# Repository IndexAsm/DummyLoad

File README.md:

# Electronic Load
A high-power, water-cooled electronic load designed for testing power supplies, batteries, converters, and other high-power electronics.

## [Board Preview]([https://kicanvas.org/?repo=https%3A%2F%2Fgithub.com%2FIndexAsm%2FDummyLoad](https://kicanvas.org/?repo=https%3A%2F%2Fgithub.com%2FIndexAsm%2FDummyLoad%2Ftree%2Fmain%2FPCB))
Note: There is a bug in the preview. It displays components from the control board next to power board, even though they are deleted in the project.

## Features
* **2 kW maximum power**
* **60 V maximum input voltage**
* **50 A maximum load current**
* **Water-cooled power stage**
* Constant-current (CC) regulation
* Multiple current ranges for improved resolution
* Designed for continuous high-power operation
* Custom-built control and measurement electronics

## Specifications

| Parameter       |             Specification |
| --------------- | ------------------------: |
| Maximum Power   |                  **2 kW** |
| Maximum Voltage |                  **60 V** |
| Maximum Current |                  **50 A** |
| Cooling         |         **Water cooling** |
| Regulation Mode | **Constant Current (CC)** |

### CC Regulation Ranges

| Current Range | Resolution |
| ------------: | ---------: |
|        0–50 A |     100 mA |
|        0–10 A |      25 mA |
|         0–5 A |      10 mA |

The selectable current ranges provide finer control at lower currents while maintaining the full **50 A** capability when required.

## Functions

* **Constant-current load (CC)**
* Selectable current ranges
* Input voltage measurement
* Load current measurement
* Power measurement
* Water-cooling system
* High-power continuous-load operation

## Applications

This electronic load is intended for testing:

* Linear and switching power supplies
* DC-DC converters
* Battery systems
* USB power supplies
* High-current power sources
* Custom power electronics

## [BOM](BOM.csv)
Total is around 600zł -> 160$

## Gallery

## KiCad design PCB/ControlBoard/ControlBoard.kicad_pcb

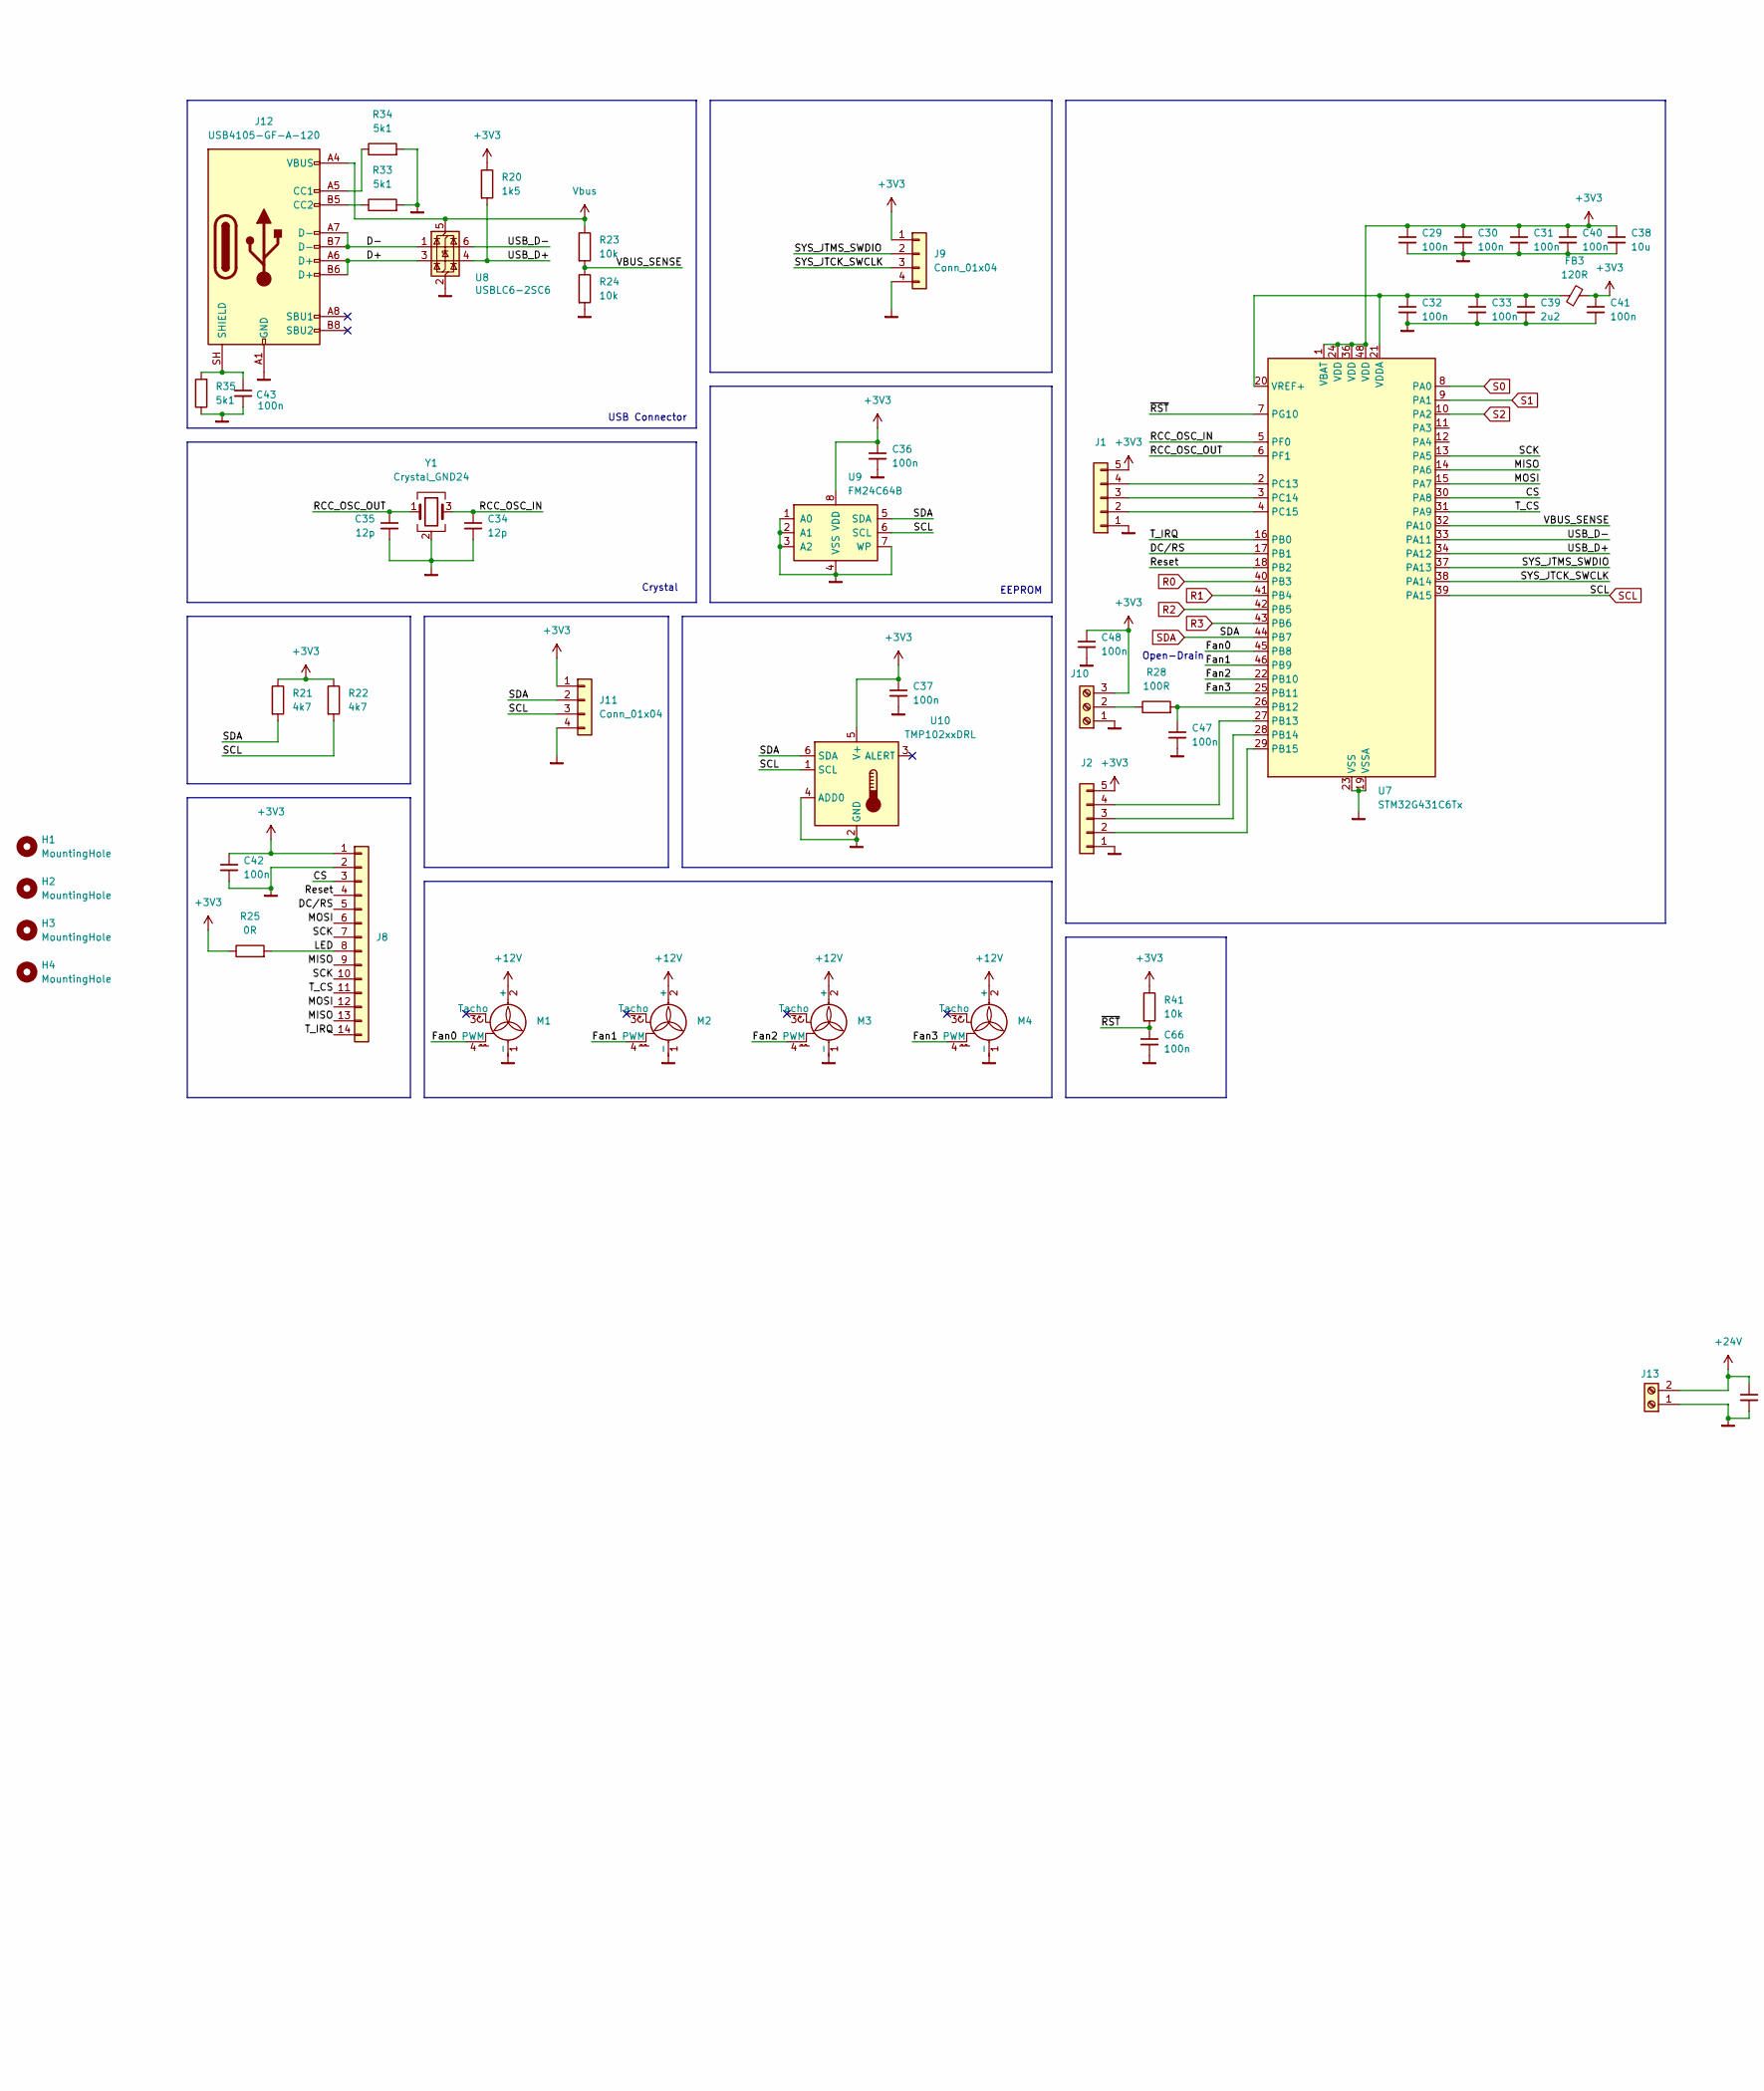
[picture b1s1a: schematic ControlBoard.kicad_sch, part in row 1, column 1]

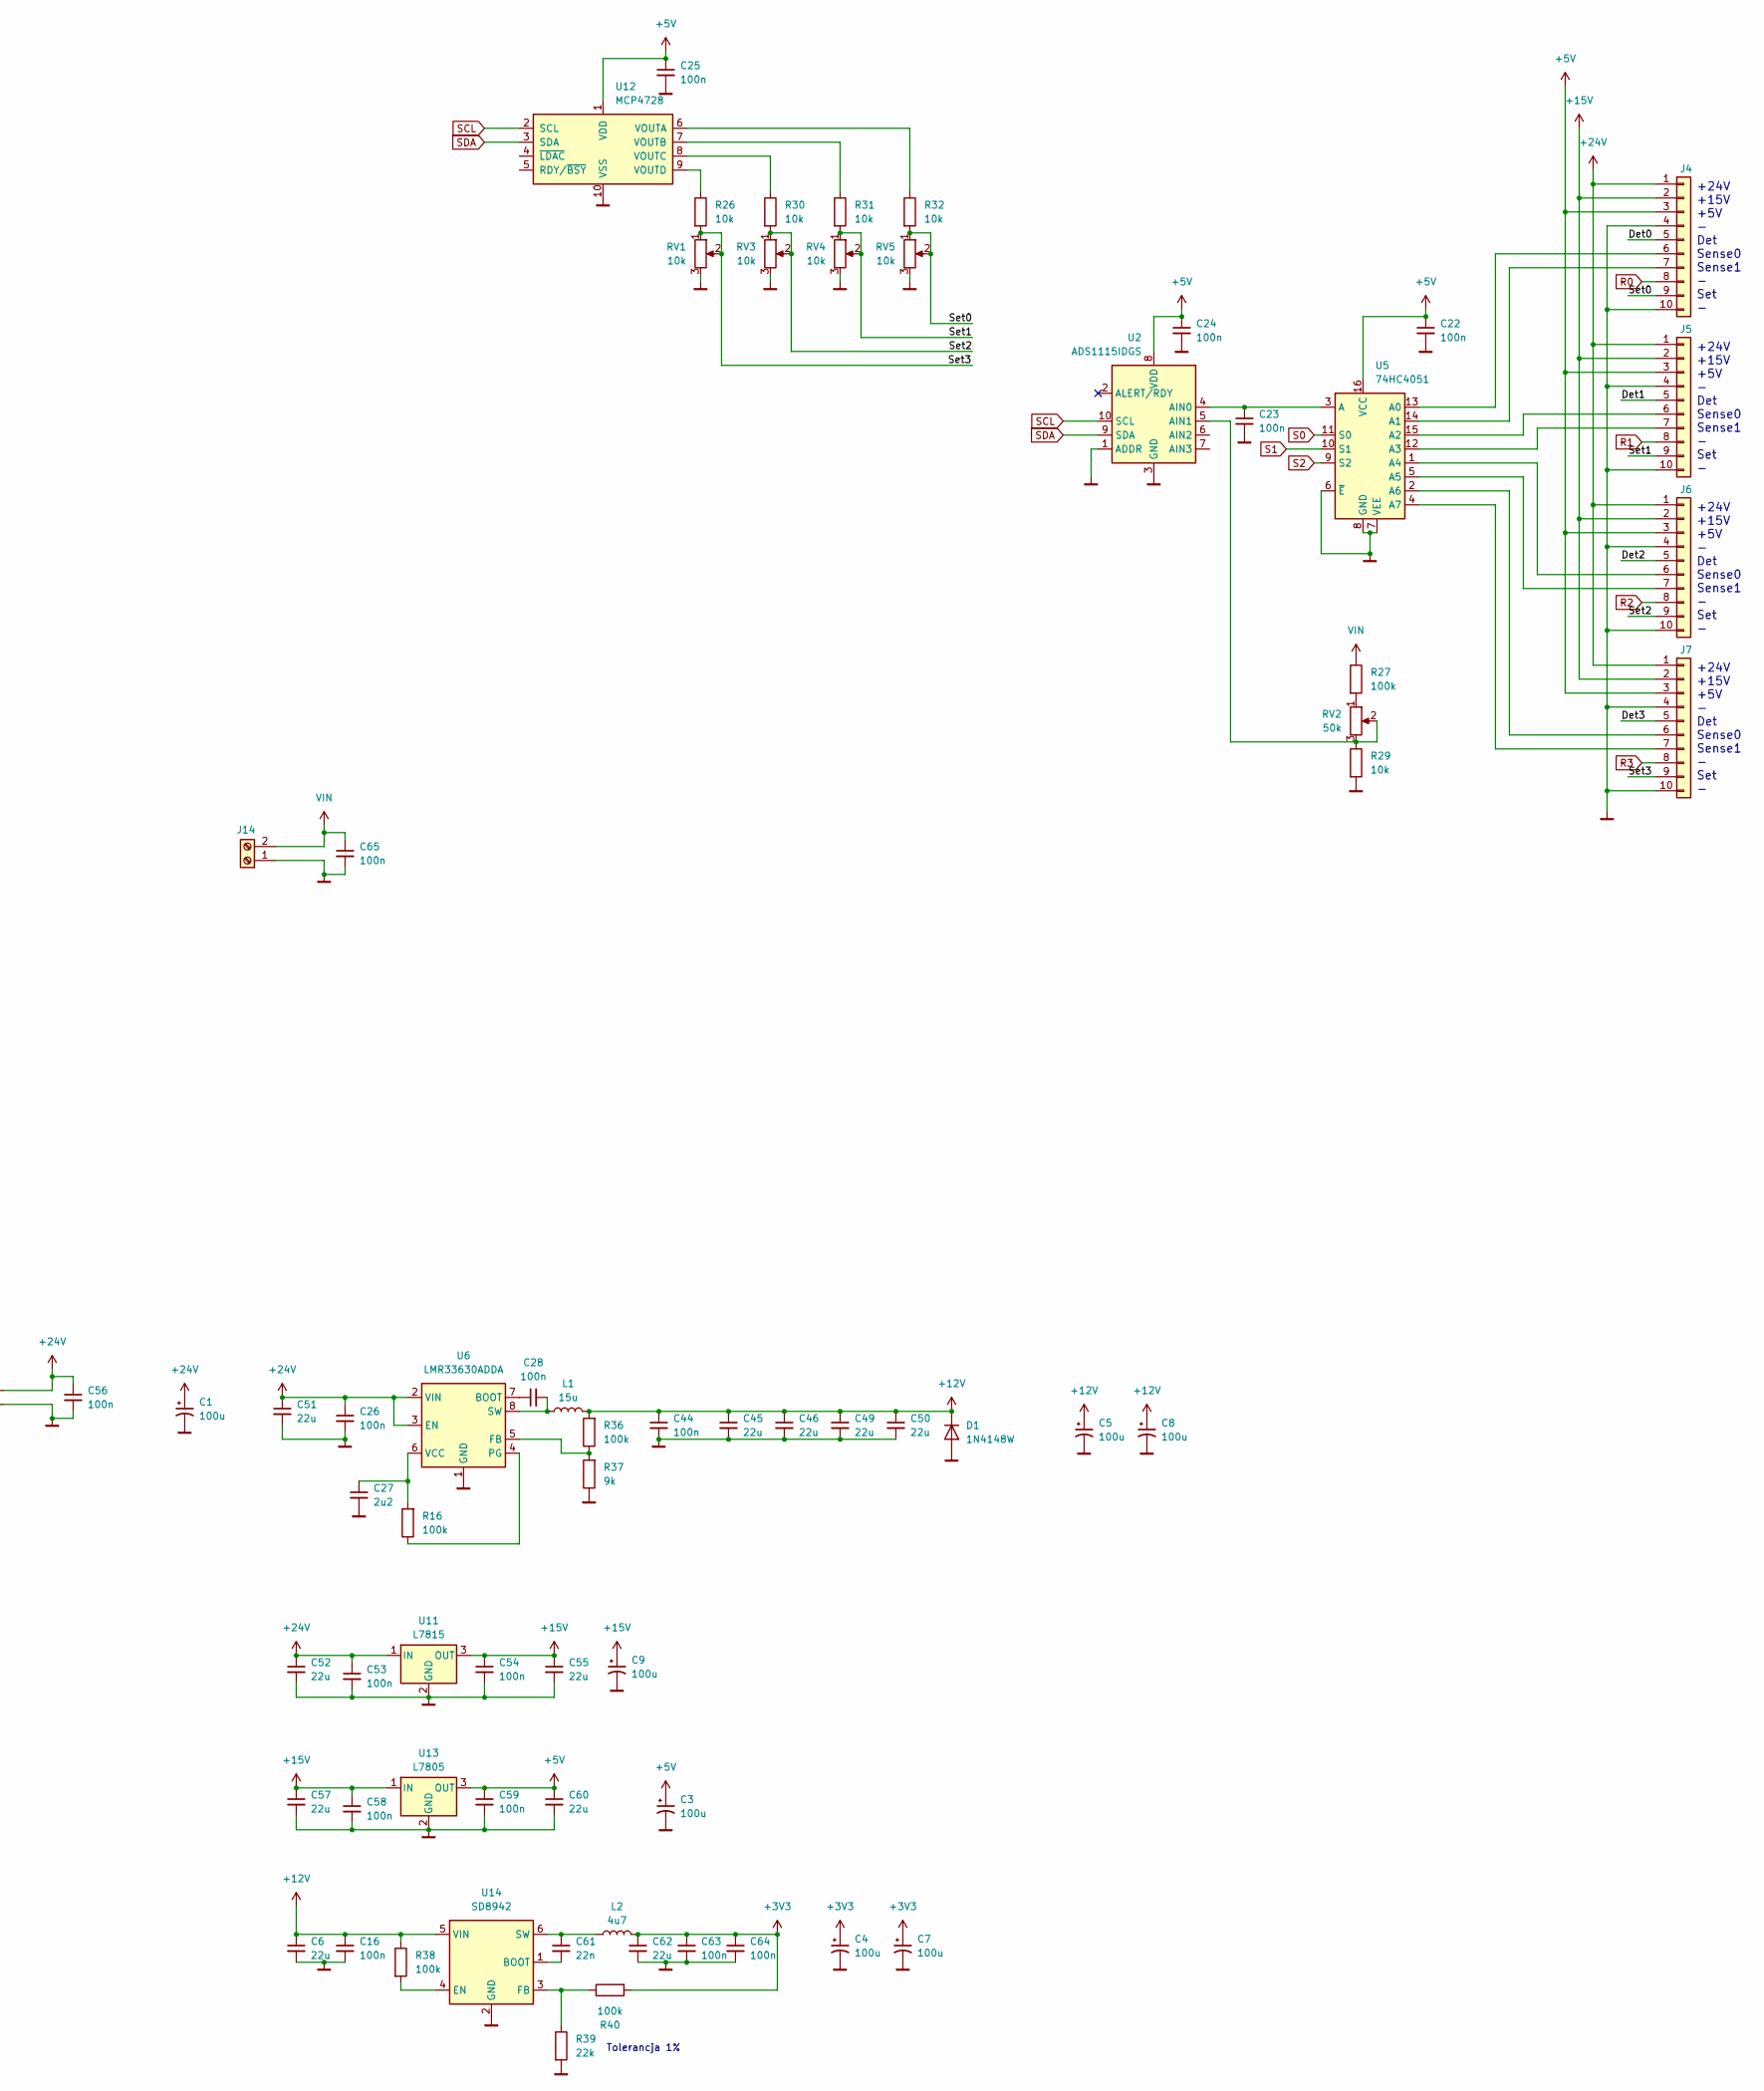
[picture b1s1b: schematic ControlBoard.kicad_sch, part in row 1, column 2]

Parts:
C1, C3, C4, C5, C7, C8, C9: 100u; CP_Radial_D6.3mm_P2.50mm
C6, C45, C46, C49, C50, C51, C52, C55, C57, C60, C62: 22u; C_1206_3216Metric
C16, C22, C23, C24, C25, C26, C28, C29, C30, C31, C32, C33, C36, C37, C40, C41, C42, C43, C44, C47, C48, C53, C54, C56, C58, C59, C63, C64, C65, C66: 100n; C_0603_1608Metric
C27, C39: 2u2; C_0603_1608Metric
C34, C35: 12p; C_0603_1608Metric
C38: 10u; C_0805_2012Metric
C61: 22n; C_0603_1608Metric
D1: 1N4148W; D_SOD-123
FB3: 120R; L_0603_1608Metric
H1, H2, H3, H4: MountingHole; MountingHole_3.2mm_M3
J1, J2: Conn_01x05; PinHeader_1x05_P2.54mm_Vertical
J4, J5, J6, J7: Conn_01x10; PinHeader_1x10_P2.54mm_Vertical
J8: Conn_01x14; PinHeader_1x14_P2.54mm_Vertical
J9, J11: Conn_01x04; PinHeader_1x04_P2.54mm_Vertical
J10: Screw_Terminal_01x03; PinHeader_1x03_P2.54mm_Vertical
J12: USB4105-GF-A-120; USB_C_Receptacle_G-Switch_GT-USB-7010ASV
J13, J14: Screw_Terminal_01x02; TerminalBlock_MaiXu_MX126-5.0-02P_1x02_P5.00mm
L1: 15u; L_APV_APH1240
L2: 4u7; L_APV_ANR5040
M1, M2, M3, M4: Fan_4pin; FanPinHeader_1x04_P2.54mm_Vertical
R16, R27, R36, R38, R40: 100k; R_0603_1608Metric
R20: 1k5; R_0603_1608Metric
R21, R22: 4k7; R_0603_1608Metric
R23, R24, R26, R29, R30, R31, R32, R41: 10k; R_0603_1608Metric
R25: 0R; R_0603_1608Metric
R28: 100R; R_0603_1608Metric
R33, R34, R35: 5k1; R_0603_1608Metric
R37: 9k; R_0603_1608Metric
R39: 22k; R_0603_1608Metric
RV1, RV3, RV4, RV5: 10k; Potentiometer_Bourns_3296W_Vertical
RV2: 50k; Potentiometer_Bourns_3296W_Vertical
U2: ADS1115IDGS; TSSOP-10_3x3mm_P0.5mm
U5: 74HC4051; SOIC-16_3.9x9.9mm_P1.27mm
U6: LMR33630ADDA; Texas_HSOP-8-1EP_3.9x4.9mm_P1.27mm_ThermalVias
U7: STM32G431C6Tx; LQFP-48_7x7mm_P0.5mm
U8: USBLC6-2SC6; SOT-23-6
U9: FM24C64B; SOIC-8_3.9x4.9mm_P1.27mm
U10: TMP102xxDRL; SOT-563
U11: L7815; TO-252-2
U12: MCP4728; MSOP-10_3x3mm_P0.5mm
U13: L7805; TO-252-2
U14: SD8942; SOT-23-6
Y1: Crystal_GND24; Crystal_SMD_EuroQuartz_X22-4Pin_2.5x2.0mm_HandSoldering

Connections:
+3V3: C4.1, C7.1, C29.1, C30.1, C31.1, C36.1, C37.1, C38.1, C40.1, C41.1, C42.1, C48.1, C62.1, C63.1, C64.1, FB3.2, J1.5, J2.5, J8.1, J9.1, J10.3, J11.1, L2.2, R20.1, R21.1, R22.1, R25.1, R40.2, R41.1, U7.1 (VBAT), U7.24 (VDD), U7.36 (VDD), U7.48 (VDD), U9.8 (VDD), U10.5 (V+)
+5V: C3.1, C22.1, C24.1, C25.1, C59.1, C60.1, J4.3, J5.3, J6.3, J7.3, U2.8 (VDD), U5.16 (VCC), U12.1 (VDD), U13.3 (OUT)
+12V: C5.1, C6.1, C8.1, C16.1, C44.1, C45.1, C46.1, C49.1, C50.1, D1.1 (K), L1.2, M1.2 (+), M2.2 (+), M3.2 (+), M4.2 (+), R36.2, R38.1, U14.5 (VIN)
+15V: C9.1, C54.1, C55.1, C57.1, C58.1, J4.2, J5.2, J6.2, J7.2, U11.3 (OUT), U13.1 (IN)
+24V: C1.1, C26.1, C51.1, C52.1, C53.1, C56.1, J4.1, J5.1, J6.1, J7.1, J13.2, U6.2 (VIN), U6.3 (EN), U11.1 (IN)
/CS: J8.3, U7.30 (PA8)
/D+: J12.A6 (D+), J12.B6 (D+), U8.3 (I/O2)
/D-: J12.A7 (D-), J12.B7 (D-), U8.1 (I/O1)
/DC/RS: J8.5, U7.17 (PB1)
/Det0: J4.5
/Det1: J5.5
/Det2: J6.5
/Det3: J7.5
/Fan0: M1.4 (PWM), U7.45 (PB8)
/Fan1: M2.4 (PWM), U7.46 (PB9)
/Fan2: M3.4 (PWM), U7.22 (PB10)
/Fan3: M4.4 (PWM), U7.25 (PB11)
/LED: J8.8, R25.2
/MISO: J8.9, J8.13, U7.14 (PA6)
/MOSI: J8.6, J8.12, U7.15 (PA7)
/RCC_OSC_IN: C34.1, U7.5 (PF0), Y1.3
/RCC_OSC_OUT: C35.1, U7.6 (PF1), Y1.1
/Reset: J8.4, U7.18 (PB2)
/SCK: J8.7, J8.10, U7.13 (PA5)
/SYS_JTCK_SWCLK: J9.3, U7.38 (PA14)
/SYS_JTMS_SWDIO: J9.2, U7.37 (PA13)
/Set0: J4.9, R32.2, RV5.1, RV5.2
/Set1: J5.9, R31.2, RV4.1, RV4.2
/Set2: J6.9, R30.2, RV3.1, RV3.2
/Set3: J7.9, R26.2, RV1.1, RV1.2
/T_CS: J8.11, U7.31 (PA9)
/T_IRQ: J8.14, U7.16 (PB0)
/USB_D+: R20.2, U7.34 (PA12), U8.4 (I/O2)
/USB_D-: U7.33 (PA11), U8.6 (I/O1)
/VBUS_SENSE: R23.2, R24.1, U7.32 (PA10)
/~RST: C66.1, R41.2, U7.7 (PG10)
Masa: C1.2, C3.2, C4.2, C5.2, C6.2, C7.2, C8.2, C9.2, C16.2, C22.2, C23.2, C24.2, C25.2, C26.2, C27.2, C29.2, C30.2, C31.2, C32.2, C33.2, C34.2, C35.2, C36.2, C37.2, C38.2, C39.2, C40.2, C41.2, C42.2, C43.2, C44.2, C45.2, C46.2, C47.2, C48.2, C49.2, C50.2, C51.2, C52.2, C53.2, C54.2, C55.2, C56.2, C57.2, C58.2, C59.2, C60.2, C62.2, C63.2, C64.2, C65.2, C66.2, D1.2 (A), J1.1, J2.1, J4.4, J4.10, J5.4, J5.10, J6.4, J6.10, J7.4, J7.10, J8.2, J9.4, J10.1, J11.4, J12.A1 (GND), J12.A12 (GND), J12.B1 (GND), J12.B12 (GND), J13.1, J14.1, M1.1 (-), M2.1 (-), M3.1 (-), M4.1 (-), R24.2, R29.2, R33.2, R34.2, R35.1, R37.1, R39.2, RV1.3, RV3.3, RV4.3, RV5.3, U2.1 (ADDR), U2.3 (GND), U5.6 (~E), U5.7 (VEE), U5.8 (GND), U6.1 (GND), U6.9 (GND), U7.19 (VSSA), U7.23 (VSS), U7.35 (VSS), U7.47 (VSS), U8.2 (GND), U9.1 (A0), U9.2 (A1), U9.3 (A2), U9.4 (VSS), U9.7 (WP), U10.2 (GND), U10.4 (ADD0), U11.2 (GND), U12.10 (VSS), U13.2 (GND), U14.2 (GND), Y1.2 (G), Y1.4 (G)
unnamed: J1.2, U7.4 (PC15)
unnamed: J1.3, U7.3 (PC14)
unnamed: J1.4, U7.2 (PC13)
unnamed: J2.2, U7.29 (PB15)
unnamed: J2.3, U7.28 (PB14)
unnamed: J2.4, U7.27 (PB13)
unnamed: J4.6, U5.13 (A0)
unnamed: J4.7, U5.14 (A1)
unnamed: J5.6, U5.15 (A2)
unnamed: J5.7, U5.12 (A3)
unnamed: J6.6, U5.1 (A4)
unnamed: J6.7, U5.5 (A5)
unnamed: J7.6, U5.2 (A6)
unnamed: J7.7, U5.4 (A7)
unnamed: J10.2, R28.1
unnamed: J12.A5 (CC1), R34.1
unnamed: J12.B5 (CC2), R33.1
unnamed: C43.1, J12.SH (SHIELD), R35.2
unnamed: R27.2, RV2.1
unnamed: C23.1, U2.4 (AIN0), U5.3 (A)
unnamed: R29.1, RV2.2, RV2.3, U2.5 (AIN1)
unnamed: C28.1, U6.7 (BOOT)
unnamed: R36.1, R37.2, U6.5 (FB)
unnamed: R16.1, U6.4 (PG)
unnamed: C28.2, L1.1, U6.8 (SW)
unnamed: C27.1, R16.2, U6.6 (VCC)
unnamed: C47.1, R28.2, U7.26 (PB12)
unnamed: C32.1, C33.1, C39.1, FB3.1, U7.20 (VREF+), U7.21 (VDDA)
unnamed: R32.1, U12.6 (VOUTA)
unnamed: R31.1, U12.7 (VOUTB)
unnamed: R30.1, U12.8 (VOUTC)
unnamed: R26.1, U12.9 (VOUTD)
unnamed: C61.2, U14.1 (BOOT)
unnamed: R38.2, U14.4 (EN)
unnamed: R39.1, R40.1, U14.3 (FB)
unnamed: C61.1, L2.1, U14.6 (SW)
R0: J4.8, U7.40 (PB3)
R1: J5.8, U7.41 (PB4)
R2: J6.8, U7.42 (PB5)
R3: J7.8, U7.43 (PB6)
S0: U5.11 (S0), U7.8 (PA0)
S1: U5.10 (S1), U7.9 (PA1)
S2: U5.9 (S2), U7.10 (PA2)
SCL: J11.3, R22.2, U2.10 (SCL), U7.39 (PA15), U9.6 (SCL), U10.1 (SCL), U12.2 (SCL)
SDA: J11.2, R21.2, U2.9 (SDA), U7.44 (PB7), U9.5 (SDA), U10.6 (SDA), U12.3 (SDA)
VIN: C65.1, J14.2, R27.1
Vbus: J12.A4 (VBUS), J12.A9 (VBUS), J12.B4 (VBUS), J12.B9 (VBUS), R23.1, U8.5 (VBUS)

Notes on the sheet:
+24V +15V +5V - Det Sense0 Sense1 - Set -
Tolerancja 1%
Crystal
Open-Drain
USB Connector
EEPROM

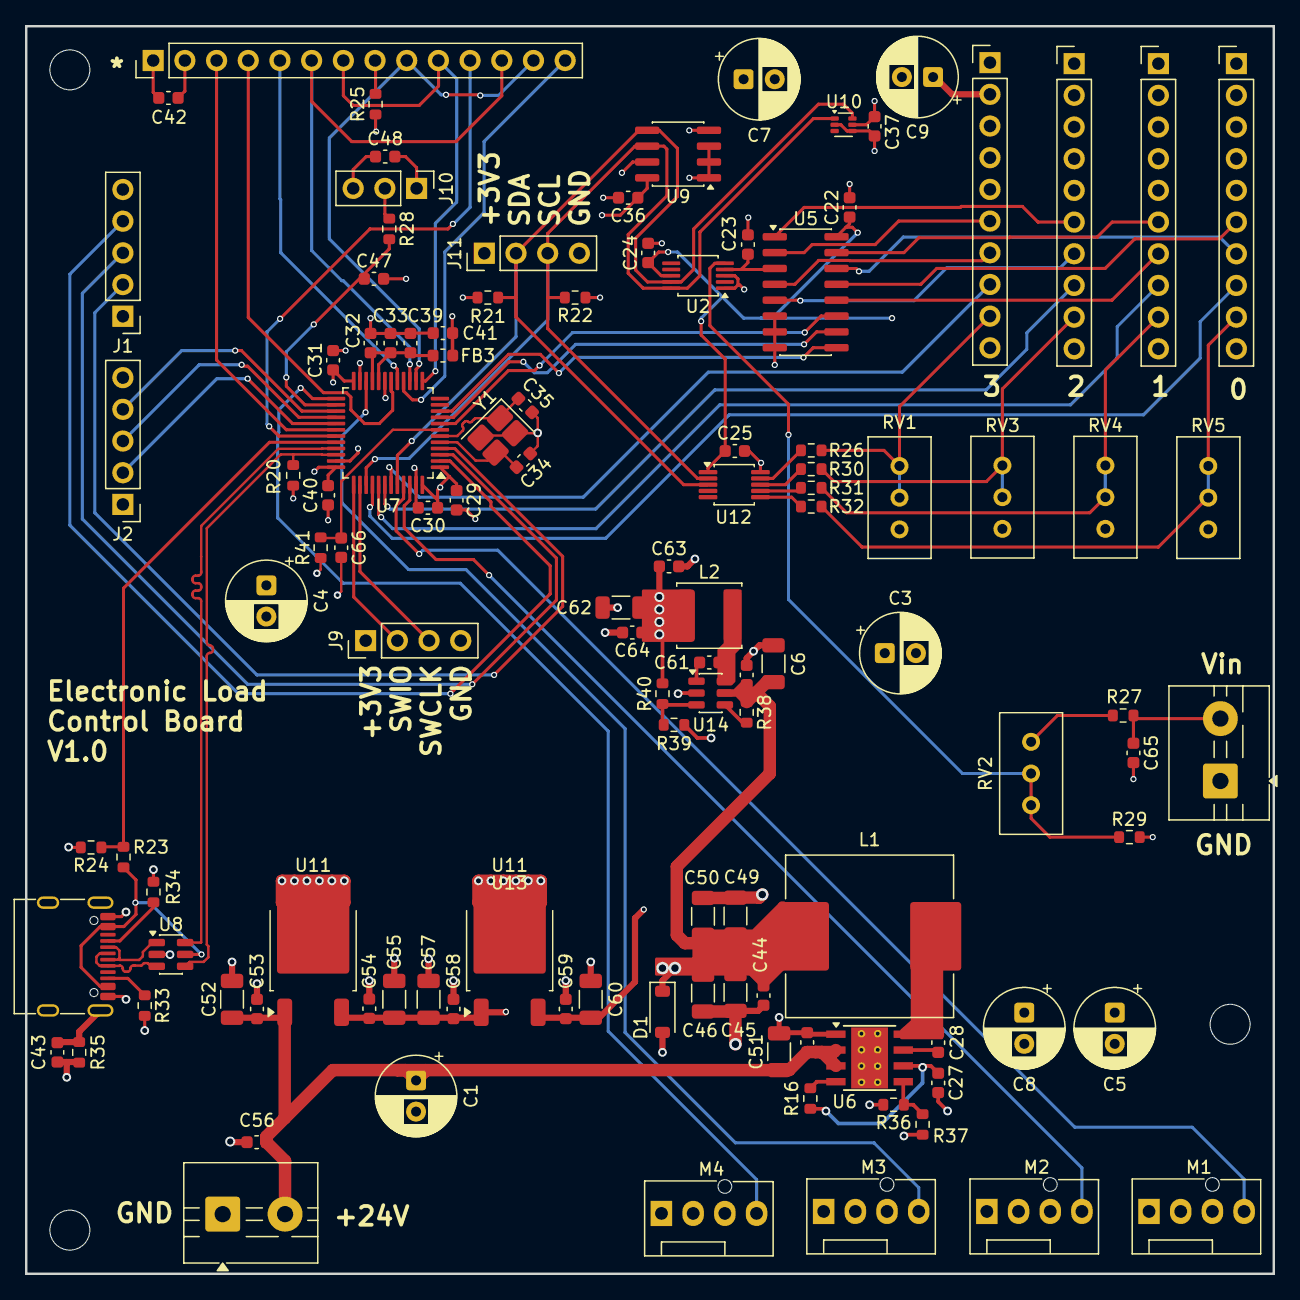
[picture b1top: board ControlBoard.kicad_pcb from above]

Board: 4 copper layers, 100.0 x 100.0 mm, 117 parts (0 on the bottom side), 80 nets.

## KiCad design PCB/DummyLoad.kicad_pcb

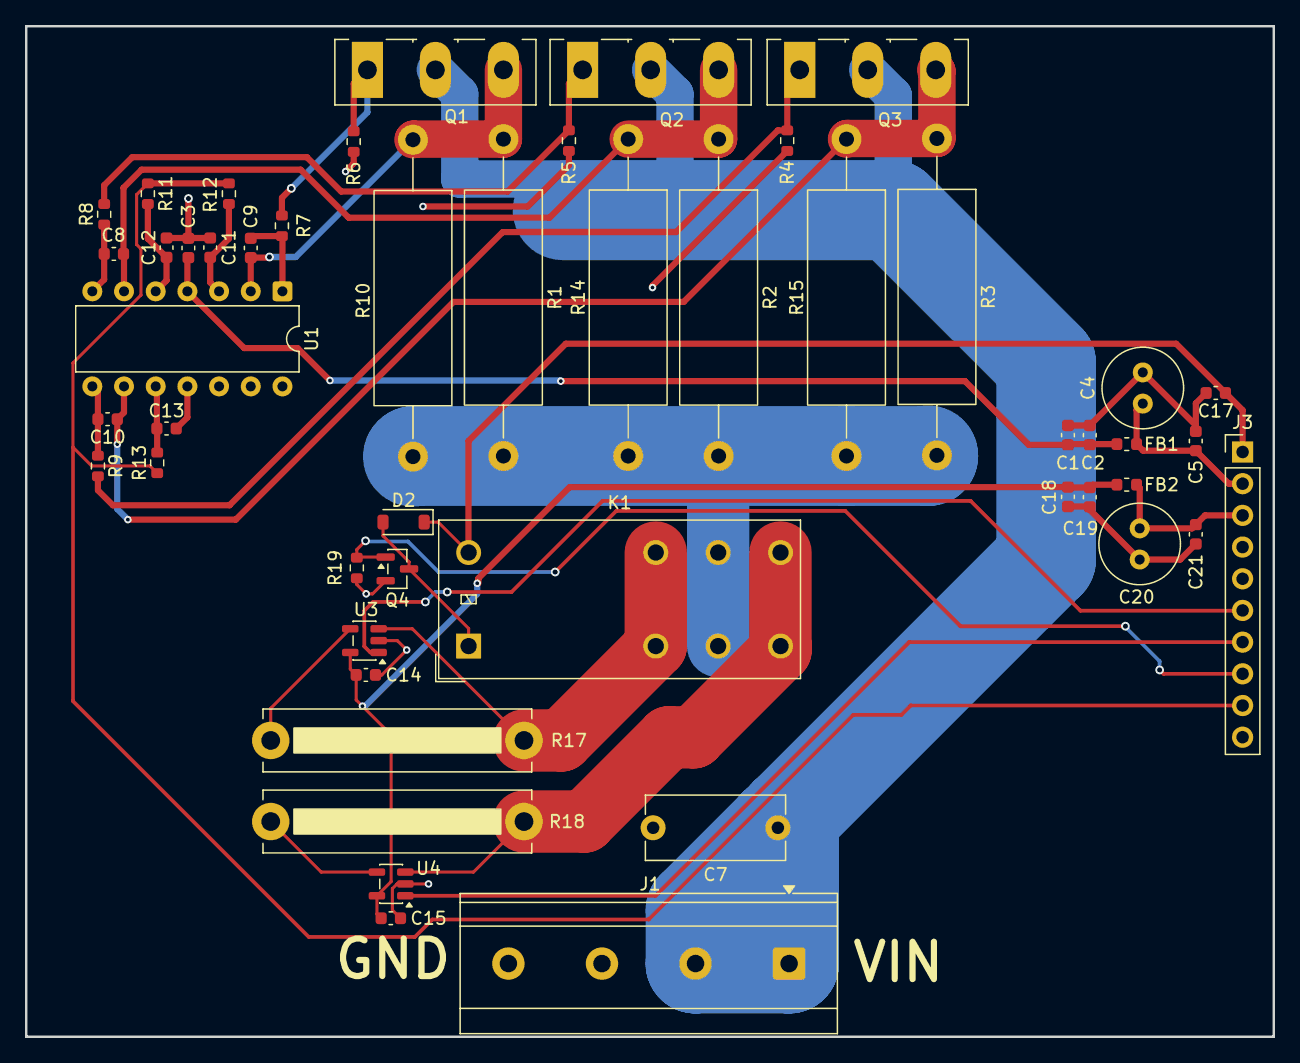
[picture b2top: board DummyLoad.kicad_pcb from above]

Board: 2 copper layers, 100.0 x 81.0 mm, 50 parts (0 on the bottom side), 27 nets.

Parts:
C1, C3, C5, C14, C15, C17, C18, C21: 100n; C_0603_1608Metric
C2, C19: 2u2; C_0603_1608Metric
C4, C20: 100u; C_Radial_D6.3mm_H7.0mm_P2.50mm
C7: 100n; C_Disc_D11.0mm_W5.0mm_P10.00mm
C8, C9, C10: 1n; C_0603_1608Metric
C11, C12, C13: 10n; C_0603_1608Metric
D2: 1N4148W; D_SOD-123
FB1, FB2: 220R; L_0603_1608Metric
J1: YK3030423000G; TerminalBlock_MetzConnect_Type175_RT02704HBLC_1x04_P7.50mm_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
J3: Conn_01x10; PinHeader_1x10_P2.54mm_Vertical
K1: G2RL-1-E; Relay_SPDT_Omron_G2RL-1-E
Q1, Q2, Q3: IRFP250N; TO-247-3_Vertical
Q4: 2N7002; SOT-23
R1, R2, R3, R10, R14, R15: 0R1; R_Axial_DIN0617_L17.0mm_D6.0mm_P25.40mm_Horizontal
R4, R5, R6, R19: 4k7; R_0603_1608Metric
R7, R8, R9: 220R; R_0603_1608Metric
R11, R12, R13: 1k; R_0603_1608Metric
R17: 0R01; R_Bare_Metal_Element_L21.3mm_W4.8mm_P20.30mm
R18: 0R1; R_Bare_Metal_Element_L21.3mm_W4.8mm_P20.30mm
U1: LM324; DIP-14_W7.62mm
U3, U4: INA180A1; SOT-23-5

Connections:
+5V: C14.1, C15.1, C18.1, C19.1, FB2.1, U3.5 (V+), U4.5 (V+)
+15V: C1.1, C2.1, C3.1, FB1.1, U1.4 (V+)
+24V: C17.1, D2.1 (K), J3.1, K1.A2
/F0: C9.1, Q1.3 (S), R1.1, R10.1, U1.2 (-)
/F1: C8.1, Q2.3 (S), R2.1, R14.1, U1.6 (-)
/F2: C10.1, Q3.3 (S), R3.1, R15.1, U1.9 (-)
/G0: Q1.1 (G), R6.1, R7.2
/G1: Q2.1 (G), R5.1, R8.2
/G2: Q3.1 (G), R4.1, R9.2
/RangeSelect: J3.8, Q4.1 (G), R19.1
/Sense0: J3.6, U3.1
/Sense1: J3.7, U4.1
/Set: J3.9, R11.1, R12.1, R13.1
Masa: C1.2, C2.2, C3.2, C4.2, C5.2, C7.2, C11.2, C12.2, C13.2, C14.2, C15.2, C17.2, C18.2, C19.2, C20.2, C21.2, J1.3, J1.4, J3.4, J3.5, J3.10, Q4.2 (S), R4.2, R5.2, R6.2, R17.2, R18.2, R19.2, U1.11 (V-), U3.2 (GND), U3.4 (-), U4.2 (GND), U4.4 (-)
unnamed: C8.2, R8.1, U1.7
unnamed: C9.2, R7.1, U1.1
unnamed: C10.2, R9.1, U1.8
unnamed: D2.2 (A), K1.A1, Q4.3 (D)
unnamed: C4.1, C5.1, FB1.2, J3.2
unnamed: C20.1, C21.1, FB2.2, J3.3
unnamed: K1.11, R1.2, R2.2, R3.2, R10.2, R14.2, R15.2
unnamed: C11.1, R12.2, U1.3 (+)
unnamed: C12.1, R11.2, U1.5 (+)
unnamed: C13.1, R13.2, U1.10 (+)
unnamed: K1.12, R17.1, U3.3 (+)
unnamed: K1.14, R18.1, U4.3 (+)
VIN: C7.1, J1.1, J1.2, Q1.2 (D), Q2.2 (D), Q3.2 (D)
